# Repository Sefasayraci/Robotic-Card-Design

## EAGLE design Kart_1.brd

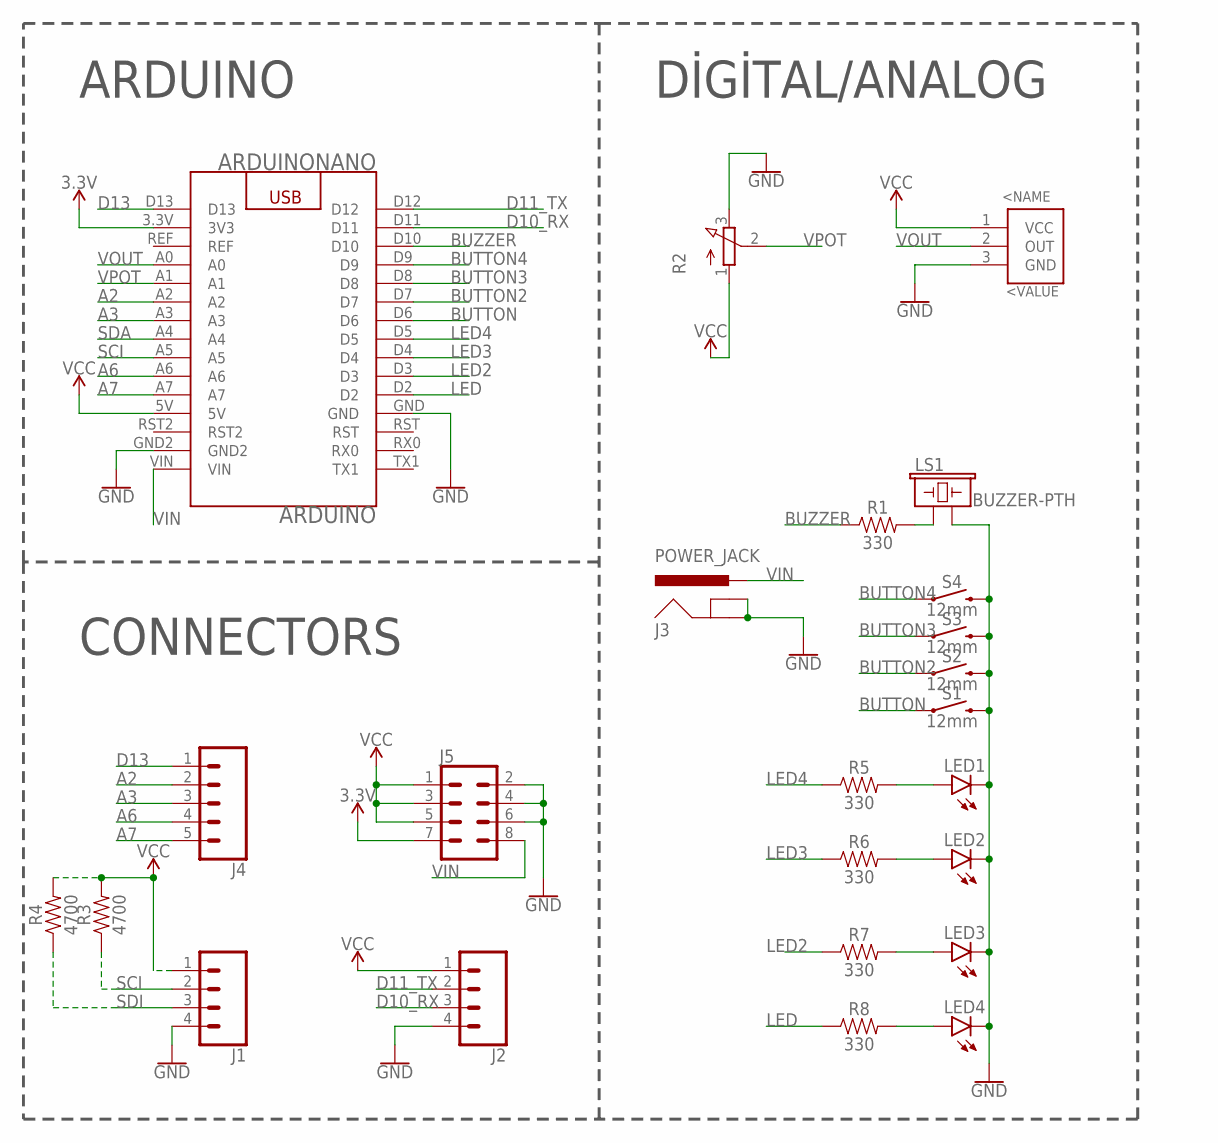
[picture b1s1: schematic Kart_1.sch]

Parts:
ARDUINO: ARDUINONANO
J1, J2: CONN_04; 1X04
J3: POWER_JACK; POWER_JACK_PTH
J4: CONN_05; 1X05
J5: CONN_04X2; 2X4
LED1, LED2, LED3, LED4: LED3MM
LM35: LM35; TO-92
LS1: BUZZER-PTH; BUZZER-12MM
R1, R5, R6, R7, R8: 330; AXIAL-0.3
R2: 3RP/1610N
R3, R4: 4700; AXIAL-0.3
S1, S2, S3, S4: 12mm; TACTILE_SWITCH_PTH_12MM

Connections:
3.3V: ARDUINO.3.3V (3V3), J5.7
A2: ARDUINO.A2, J4.2
A3: ARDUINO.A3, J4.3
A6: ARDUINO.A6, J4.4
A7: ARDUINO.A7, J4.5
BUTTON: ARDUINO.D6, S1.1
BUTTON2: ARDUINO.D7, S2.1
BUTTON3: ARDUINO.D8, S3.1
BUTTON4: ARDUINO.D9, S4.1
BUZZER: ARDUINO.D10, R1.P$1 (1)
D10_RX: ARDUINO.D11, J2.3
D11_TX: ARDUINO.D12, J2.2
D13: ARDUINO.D13, J4.1
GND: ARDUINO.GND, ARDUINO.GND2, J1.4, J2.4, J3.GND, J3.GNDBREAK, J5.2, J5.4, J5.6, LED1.K (C), LED2.K (C), LED3.K (C), LED4.K (C), LM35.3 (GND), LS1.- (2), R2.3 (E), S1.3 (2), S2.3 (2), S3.3 (2), S4.3 (2)
LED: ARDUINO.D2, R8.P$1 (1)
LED2: ARDUINO.D3, R7.P$1 (1)
LED3: ARDUINO.D4, R6.P$1 (1)
LED4: ARDUINO.D5, R5.P$1 (1)
unnamed: LS1.+ (1), R1.P$2 (2)
unnamed: LED1.A, R5.P$2 (2)
unnamed: LED2.A, R6.P$2 (2)
unnamed: LED3.A, R7.P$2 (2)
unnamed: LED4.A, R8.P$2 (2)
SCI: ARDUINO.A5, J1.2, R3.P$1 (1)
SDA: ARDUINO.A4
SDI: J1.3, R4.P$1 (1)
VCC: ARDUINO.5V, J1.1, J2.1, J5.1, J5.3, J5.5, LM35.1 (VCC), R2.1 (A), R3.P$2 (2), R4.P$2 (2)
VIN: ARDUINO.VIN, J3.PWR, J5.8
VOUT: ARDUINO.A0, LM35.2 (OUT)
VPOT: ARDUINO.A1, R2.2 (S)

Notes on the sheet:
ARDUINO
CONNECTORS
DİGİTAL/ANALOG

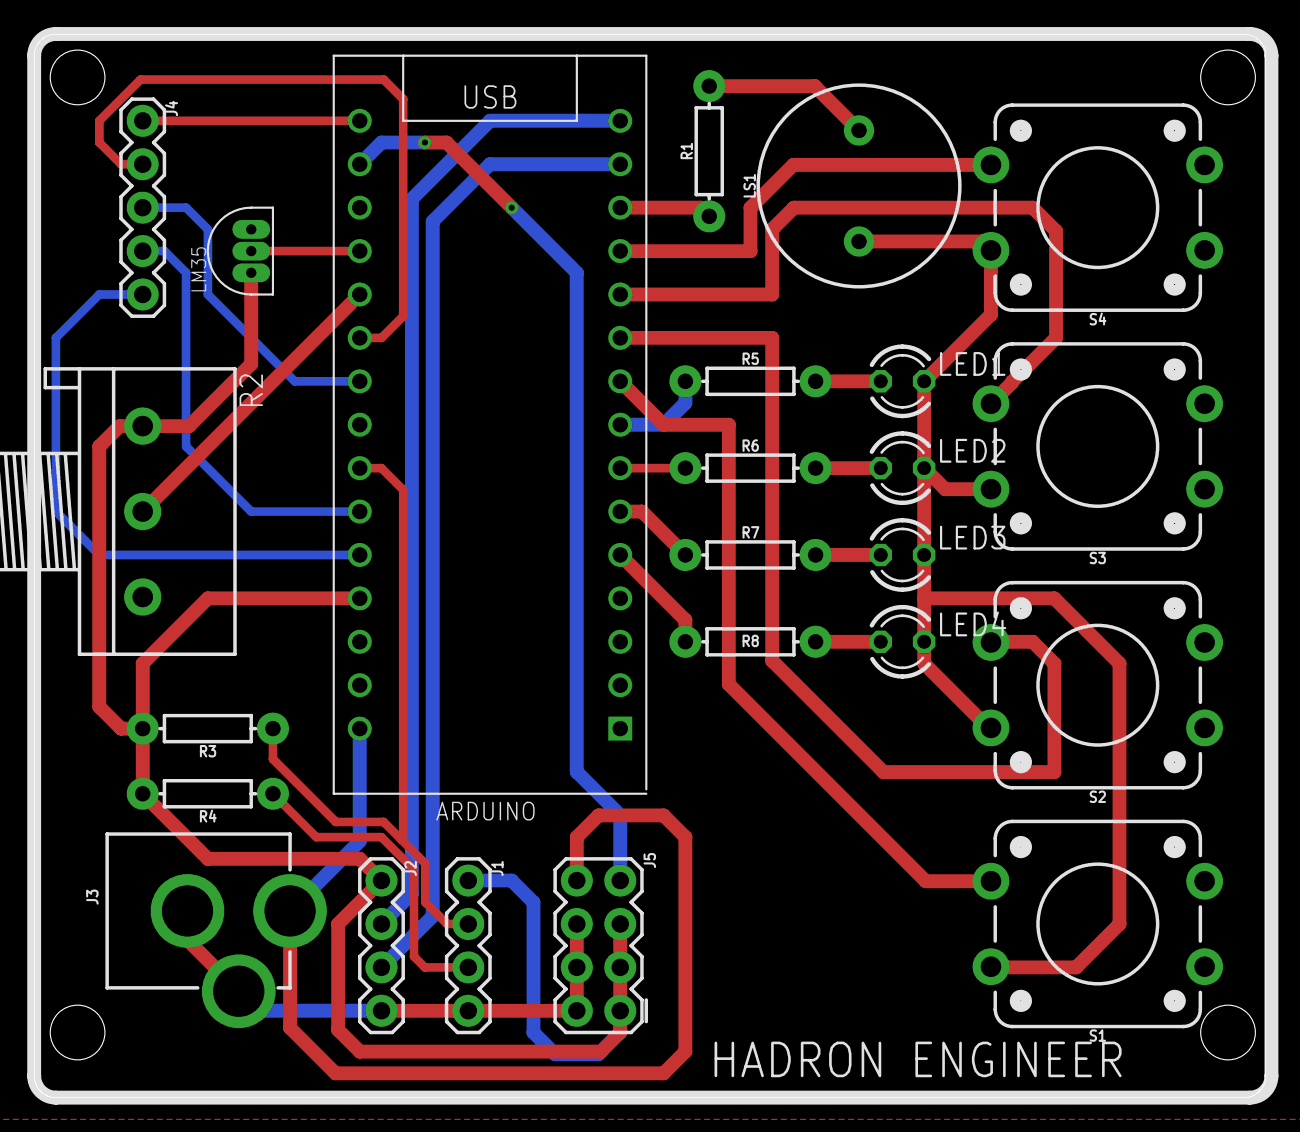
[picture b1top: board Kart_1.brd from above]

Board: 2 copper layers, 72.1 x 62.2 mm, 24 parts (0 on the bottom side), 29 nets.

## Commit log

2021-04-03 Card Design_1 Eagle, Robotic System

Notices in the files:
parts and their libraries:
SparkFun-Switches: Licensing: Creative Commons ShareAlike 4.0 International - https://creativecommons.org/licenses/by-sa/4.0
